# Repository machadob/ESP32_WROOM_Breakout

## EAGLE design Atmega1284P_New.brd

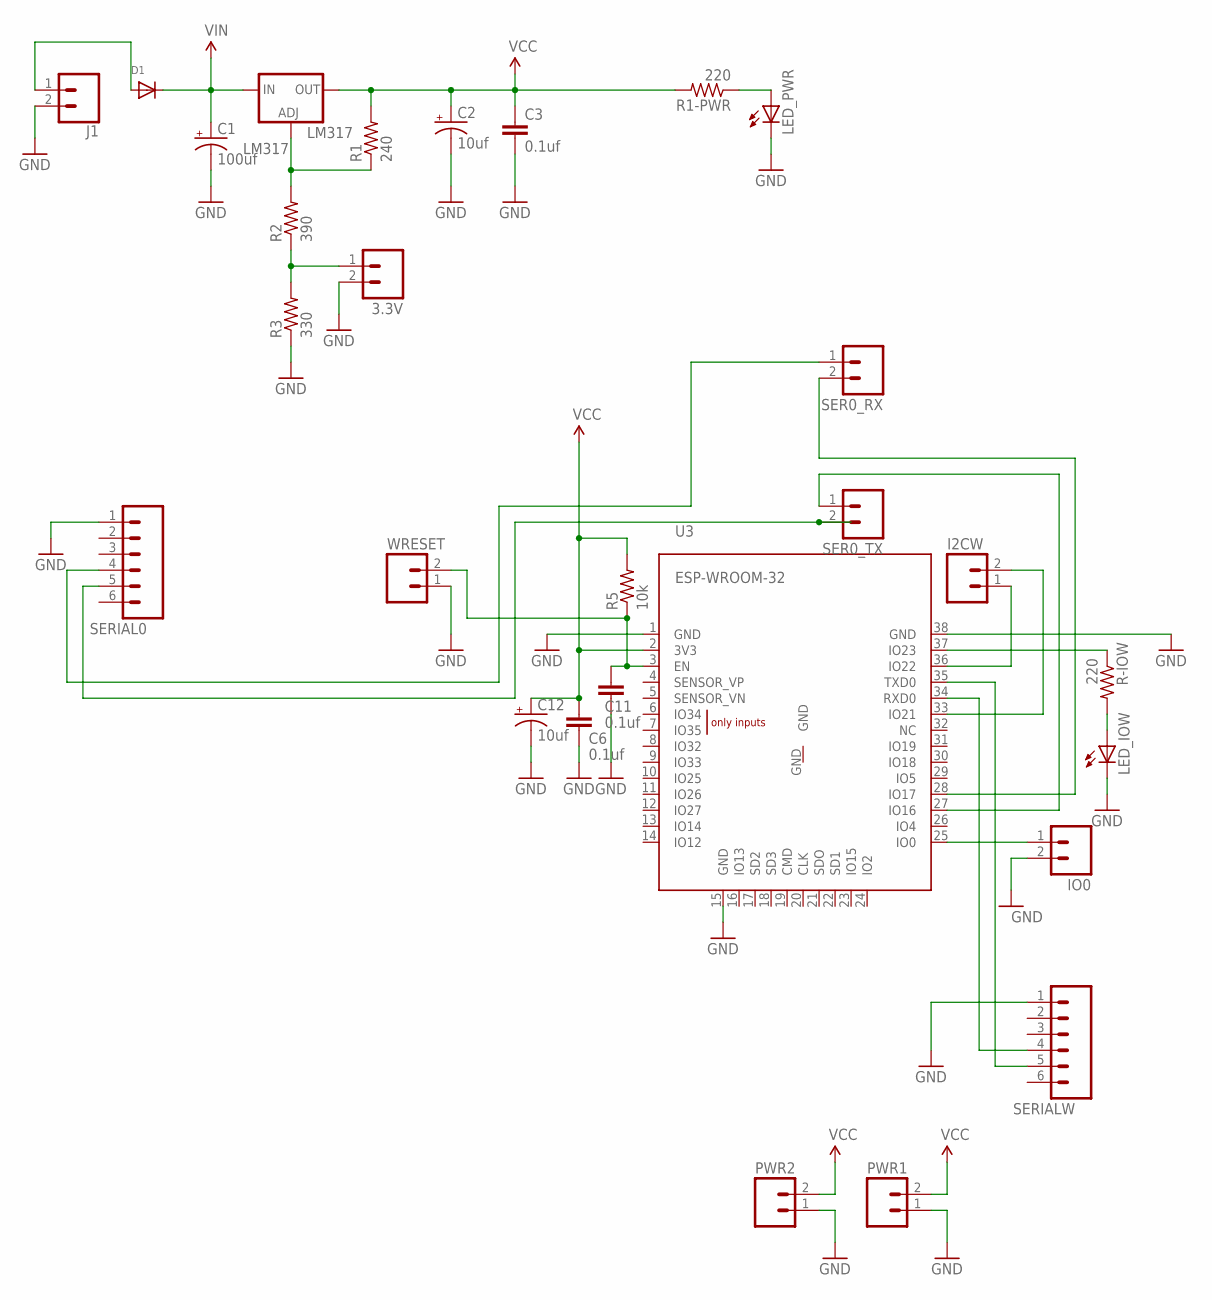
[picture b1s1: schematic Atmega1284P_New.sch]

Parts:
3.3V: M02PTH; 1X02@1
C1: 100uf; PANASONIC_D
C2, C12: 10uf; PANASONIC_D
C3, C6, C11: 0.1uf; 0805
D1: DIODE_SOD-123FL; SOD-123FL
I2CW: M02PTH; 1X02@1
IO0: M02PTH; 1X02@1
J1: CONN_023.5MM; SCREWTERMINAL-3.5MM-2
LED_IOW: LEDCHIPLED_0805; CHIPLED_0805
LED_PWR: LEDCHIPLED_0805; CHIPLED_0805
LM317: LM317; SOT223
PWR1, PWR2: M02PTH; 1X02@1
R1: 240; R0805
R1-PWR: 220; R0805
R2: 390; R0805
R3: 330; R0805
R5: 10k; R0805
R-IOW: 220; R0805
SER0_RX, SER0_TX: M02PTH; 1X02@1
SERIAL0: M06SILK_FEMALE_PTH; 1X06
SERIALW: M06SILK_FEMALE_PTH; 1X06
U3: ESP-WROOM-32
WRESET: M02PTH; 1X02@1

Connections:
GND: 3.3V.2, C1.-, C2.-, C3.2, C6.2, C11.2, C12.-, IO0.2, J1.2, LED_IOW.C, LED_PWR.C, PWR1.1, PWR2.1, R3.1, SERIAL0.1, SERIALW.1, U3.1 (GND), U3.15 (GND), U3.38 (GND), WRESET.1
unnamed: 3.3V.1, R2.1, R3.2
unnamed: SER0_RX.1, SERIAL0.4
unnamed: SER0_TX.2, SERIAL0.5
unnamed: LM317.1 (ADJ), R1.1, R2.2
unnamed: LED_PWR.A, R1-PWR.1
unnamed: C11.1, R5.1, U3.3 (EN), WRESET.2
unnamed: IO0.1, U3.25 (IO0)
unnamed: SERIALW.4, U3.34 (RXD0)
unnamed: SERIALW.5, U3.35 (TXD0)
unnamed: R-IOW.1, U3.37 (IO23)
unnamed: LED_IOW.A, R-IOW.2
unnamed: I2CW.2, U3.33 (IO21)
unnamed: I2CW.1, U3.36 (IO22)
unnamed: SER0_RX.2, U3.28 (IO17)
unnamed: D1.A, J1.1
unnamed: SER0_TX.1, U3.27 (IO16)
VCC: C2.+, C3.1, C6.1, C12.+, LM317.2 (OUT), PWR1.2, PWR2.2, R1.2, R1-PWR.2, R5.2, U3.2 (3V3)
VIN: C1.+, D1.C, LM317.3 (IN)

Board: 2 copper layers, 28 parts (0 on the bottom side), 19 nets, no tracks yet.

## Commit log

2021-04-25 GOOD_Working_Copy
2021-04-25 Cleaned up
2021-04-25 Working Copy
2021-04-26 Good Working copy

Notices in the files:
parts and their libraries:
SparkFun-Connectors: Licensing: Creative Commons ShareAlike 4.0 International - https://creativecommons.org/licenses/by-sa/4.0
